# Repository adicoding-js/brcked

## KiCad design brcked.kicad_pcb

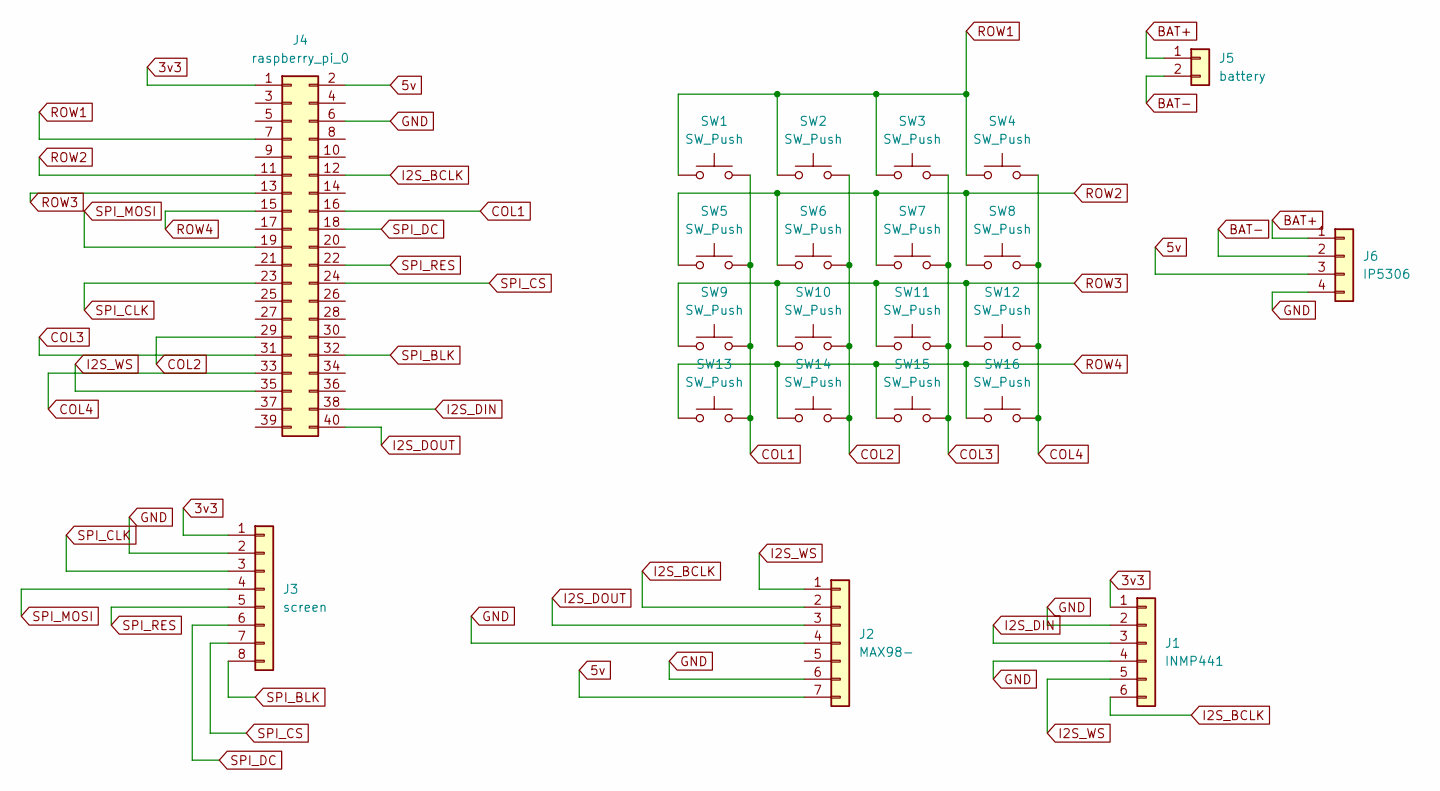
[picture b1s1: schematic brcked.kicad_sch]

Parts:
J1: INMP441; PinHeader_1x06_P2.54mm_Vertical
J2: MAX98-; PinHeader_1x07_P2.54mm_Vertical
J3: screen; PinHeader_1x08_P2.54mm_Vertical
J4: raspberry_pi_0; PinHeader_2x20_P2.54mm_Vertical
J5: battery; PinHeader_1x02_P2.54mm_Vertical
J6: IP5306; PinHeader_1x04_P2.54mm_Vertical
SW1, SW2, SW3, SW4, SW5, SW6, SW7, SW8, SW9, SW10, SW11, SW12, SW13, SW14, SW15, SW16: SW_Push; SW_PUSH_6mm

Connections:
3v3: J1.1, J3.1, J4.1
5v: J2.7, J4.2, J6.3
BAT+: J5.1, J6.1
BAT-: J5.2, J6.2
COL1: J4.16, SW1.2, SW5.2, SW9.2, SW13.2
COL2: J4.29, SW2.2, SW6.2, SW10.2, SW14.2
COL3: J4.31, SW3.2, SW7.2, SW11.2, SW15.2
COL4: J4.33, SW4.2, SW8.2, SW12.2, SW16.2
GND: J1.2, J1.4, J2.4, J2.6, J3.2, J4.6, J6.4
I2S_BCLK: J1.6, J2.2, J4.12
I2S_DIN: J1.3, J4.38
I2S_DOUT: J2.3, J4.40
I2S_WS: J1.5, J2.1, J4.35
ROW1: J4.7, SW1.1, SW2.1, SW3.1, SW4.1
ROW2: J4.11, SW5.1, SW6.1, SW7.1, SW8.1
ROW3: J4.13, SW9.1, SW10.1, SW11.1, SW12.1
ROW4: J4.15, SW13.1, SW14.1, SW15.1, SW16.1
SPI_BLK: J3.8, J4.32
SPI_CLK: J3.3, J4.23
SPI_CS: J3.7, J4.24
SPI_DC: J3.6, J4.18
SPI_MOSI: J3.4, J4.19
SPI_RES: J3.5, J4.22

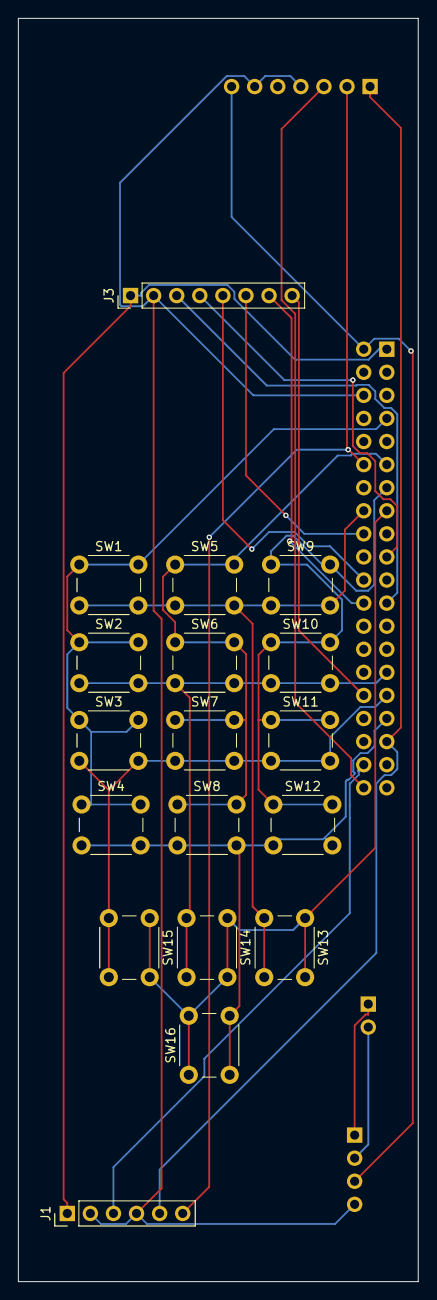
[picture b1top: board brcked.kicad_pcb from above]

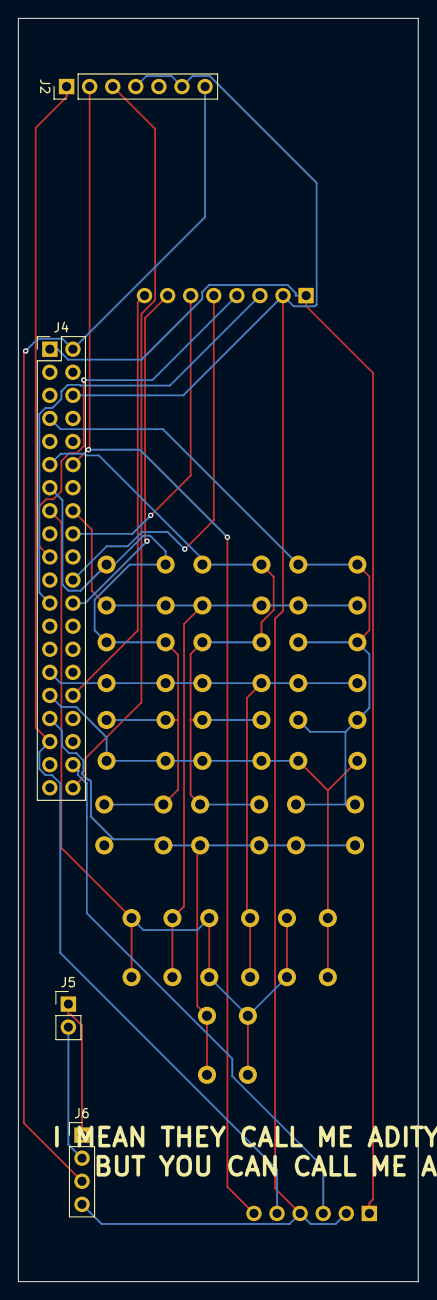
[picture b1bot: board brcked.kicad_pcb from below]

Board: 2 copper layers, 44.0 x 139.0 mm, 22 parts (4 on the bottom side), 23 nets.
